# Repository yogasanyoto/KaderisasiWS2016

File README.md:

# KaderisasiWS2016
###Repository untuk keperluan calon kru WS HME ITB 2016
1. **Informasi Umum**
  * Presentasi dan spesifikasi tugas tiap day dapat dilihat pada folder day yang bersesuaian
  * Pembagian kelompok beserta mentor-mentornya dapat dilihat [disini](https://github.com/WorkshopHMEITB/KaderisasiWS2016/blob/master/KelompokCakruWS2016.csv)
  * Kontak mentor dapat dilihat [disini](https://github.com/WorkshopHMEITB/KaderisasiWS2016/blob/master/KontakMentorCakruWS2016.csv)
2. **Aturan umum pengumpulan tugas**
  * Tugas yang sudah selesai harus dipresentasikan kepada mentor masing-masing kelompok pada waktu yang ditentukan bersama mentor sebelum batas waktu yang diberikan pada spesifikasi tugas
  * Tugas harus disertai dengan dokumentasi tugas menggunakan template dokumentasi yang ada pada repository KaderisasiWS2016
  * File-file terkait (yang akan diberitahu pada spesifikasi tiap tugas) beserta dokumentasinya harus dikumpulkan melalui repository KaderisasiWS2016 sebelum batas waktu yang diberikan pada spesifikasi tugas (cara pengumpulan tugas ke repository ada pada poin 3 file ini)
  * Telat mempresentasikan kepada mentor akan mengakibatkan pengurangan nilai total sebesar 5% (telat 1 hari), 15% (telat 2 hari), 30% (telat 3 hari), dan 50% (dengan kata lain tidak dianggap mengumpulkan jika telat lebih dari 4 hari)
3. **Cara pengumpulan tugas**<br  />
 1. Jika anda belum terdaftar di github, klik tombol ***Sign up*** di pojok kanan atas [page ini](https://github.com/WorkshopHMEITB/KaderisasiWS2016) dan ikuti terus prosedurnya hingga anda terdaftar
 2. Jika anda sudah terdaftar, *sign in* dengan menekan tombol ***Sign in*** di pojok kanan atas [page ini](https://github.com/WorkshopHMEITB/KaderisasiWS2016)
 3. Klik tombol ***Fork*** di pojok kanan atas [page ini](https://github.com/WorkshopHMEITB/KaderisasiWS2016)
 4. *Pop up window* akan muncul setelah anda menekan tombol *Fork*, tekan ***profil anda***.
 5. Sekarang, *repository* baru (yang merupakan *forked* repository [WorkshopHMEITB/KaderisasiWS2016](https://github.com/WorkshopHMEITB/KaderisasiWS2016)) akan muncul di profil anda. Alamat repository tersebut akan berbentuk seperti ini: https://github.com/USER_NAME/KaderisasiWS2016, sebagai contoh, https://github.com/fuad1502/KaderisasiWS2016. (Jika anda baru saja mem-*fork* repository WorkshopHMEITB/KaderisasiWS2016, anda akan langsung ter-*redirect* ke alamat repository baru anda tersebut)
 6. Setelah *forked repository* berhasil anda buat, anda dapat ***mengupload file-file*** yang harus anda upload ke repository tersebut. Cara mengupload file yang baik dan benar, ada pada bagian 4, "Cara mengupload file-file ke forked repository"
 7. Setelah semua file yang diperlukan sudah anda upload, tekan ***New Pull Request***
 8. Kemudian tekan tombol ***Create pull request***. Tuliskan "Tugas Day X" pada bagian title dan tekan kembali tombol ***Create pull request***
 9. Selesai. Jika anda sudah mengupload semua file dengan benar, pihak kami akan menerima *pull request* anda dan menggabungkannya ke dalam repository [WorkshopHMEITB/KaderisasiWS2016](https://github.com/WorkshopHMEITB/KaderisasiWS2016)
4. **Cara mengupload file-file ke forked repository**
 1. Buka *forked repository* anda di https://github.com/USER_NAME/KaderisasiWS2016
 2. Buka folder day yang bersesuaian
 3. Buat folder pengumpulan tugas kelompok anda di dalam folder day tersebut dengan cara sebagai berikut
     * Tekan tombol ***Create new file***
     * Pada bagian "Name your file...", tulis "KelompokX" (ganti X dengan nomor kelompok anda), lalu tekan "/". Kemudian, tulis lagi ".gitkeep"
     * *Scroll* kebawah dan klik ***Commit new file***
 4. Pada folder pengumpulan tugas kelompok anda tersebut, klik tombol ***Upload files***
 5. Klik ***choose your files*** dan pilih file mana saja yang ingin anda upload
 6. Setelah semua file berhasil diupload, tekan tombol ***Commit changes***

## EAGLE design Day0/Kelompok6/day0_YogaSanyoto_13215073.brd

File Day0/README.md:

#Tugas Day 0
###*Template file dokumentasi belum ada, kerjakan saja file skematik dan PCB nya dahulu*
1. **Detail Tugas**
  1. Membuat file skematik dari rangkaian di bawah ini menggunakan software Eagle<br  />
  
  2. Membuat file PCB dari skematik yang telah dibuat menggunakan software Eagle
  3. Mencetak 1 buah PCB dari file PCB yang telah dibuat
  4. Membeli komponen-komponen yang dibutuhkan dan memasangnya/menyoldernya pada PCB yang telah dicetak
  5. Membuat dan mengupload file dokumentasi ke folder yang sesuai di repository [KaderisasiWS2016](https://github.com/WorkshopHMEITB/KaderisasiWS2016) (caranya dapat dilihat pada file [README.md](https://github.com/WorkshopHMEITB/KaderisasiWS2016/blob/master/README.md) pada root directory repository)
  6. Mengupload file-file terkait ke folder yang sesuai di repository [KaderisasiWS2016](https://github.com/WorkshopHMEITB/KaderisasiWS2016). File-file yang dimaksud ialah sebagai berikut.
    * File Skematik
    * File PCB
2. **Parameter Penilaian**<br  />
Coming soon...
3. **Deadline**<br  />
Sabtu 17/9/2016 (Namun mengumpulkan minggu tidak dihitung telat satu hari untuk tugas ini, dikarenakan PCB tidak mungkin selesai hari minggu)
4. **Informasi Tambahan**
  * Software Eagle dapat didownload secara gratis sebagai *freeware* dari https://cadsoft.io/
  * Rangkaian yang diberikan diatas sulit untuk dimengerti dikarenakan pengintegrasian 4 komponen transistor dalam rangkaian kedalam satu IC CA3046. Berikut adalah gambar skematik rangkaian diatas apabila keempat transistor digambarkan satu per satu. <br  />
  
  * Tips untuk Mempermudah Pengerjaan
    * Manfaatkan fitur DRC pada pembuatan file PCB untuk memastikan desain yang anda buat dapat dicetak oleh tempat pencetakan anda
    * Gunakan ground plane untuk mempermudah routing (Tidak harus)
    * Gunakan IC header untuk memastikan IC tidak akan rusak saat proses penyolderan, serta agar IC dapat dilepas untuk dipakai dalam hal lain (Tidak harus)
    * Untuk mengurangi biaya mencetak PCB, ketika ingin mencetak, cetak PCB beberapa kelompok secara bersama-sama
    * Cetak maksimal 3 hari sebelum deadline jika pakai masking (Kamis, 15/9/2016), 2 hari jika tidak. Untuk jaga-jaga.
  * Informasi Pencetakan PCB
    * *Spectra* 
      * Lokasi : https://goo.gl/maps/9tBonaAyMZR2
      * Email : kng@bdg.centrin.net.id
      * Telepon : 022 - 7322667
      * Teknologi : Ukuran jalur minimum 0.2 mm (kalau mau aman 0.25 mm)
      * Dapat mencetak langsung ke tempatnya dengan membawa file PCB, atau dapat melalui email dan transfer ATM
    * *MultiKarya* 
      * Lokasi : https://goo.gl/maps/EgyCBrZe8uH2
      * Website : www.multikarya.com
      * Email : pcb_multikarya@yahoo.com
      * Telepon : 022 - 720 2852
      * Teknologi : lihat lengkapnya di http://www.multikarya.com/pcb_technical_indonesia.html
    * *Selc* 
      * Lokasi : https://goo.gl/maps/5XCbfng3uKE2
      * Website : www.selc-komponen.co.id
      * Email : selc@bdg.centrin.net.id
      * Telepon : 022 - 721 0909
      * Teknologi : lihat lengkapnya di http://www.selc-komponen.co.id/index.php?route=information/information&information_id=7)
  * Informasi Pembelian Komponen
    * *Anam* (https://goo.gl/maps/y4qWtzdkQtB2 sebelah Balubur Town Square)
    * *Jaya Plaza* (https://goo.gl/maps/nTADkQ1KY322)<br  />
    Jika kesulitan dalam menemukan CA3046, dapat ditemukan di toko i.want.electronics di Jaya Plaza dengan harga Rp. 27500
    * *Duta Irama* (https://goo.gl/maps/VzKpAT1tsW42 depan Jaya Plaza)
  * Jika ada pertanyaan silakan hubungi [mentor masing-masing](https://github.com/WorkshopHMEITB/KaderisasiWS2016/blob/master/KontakMentorCakruWS2016.csv)

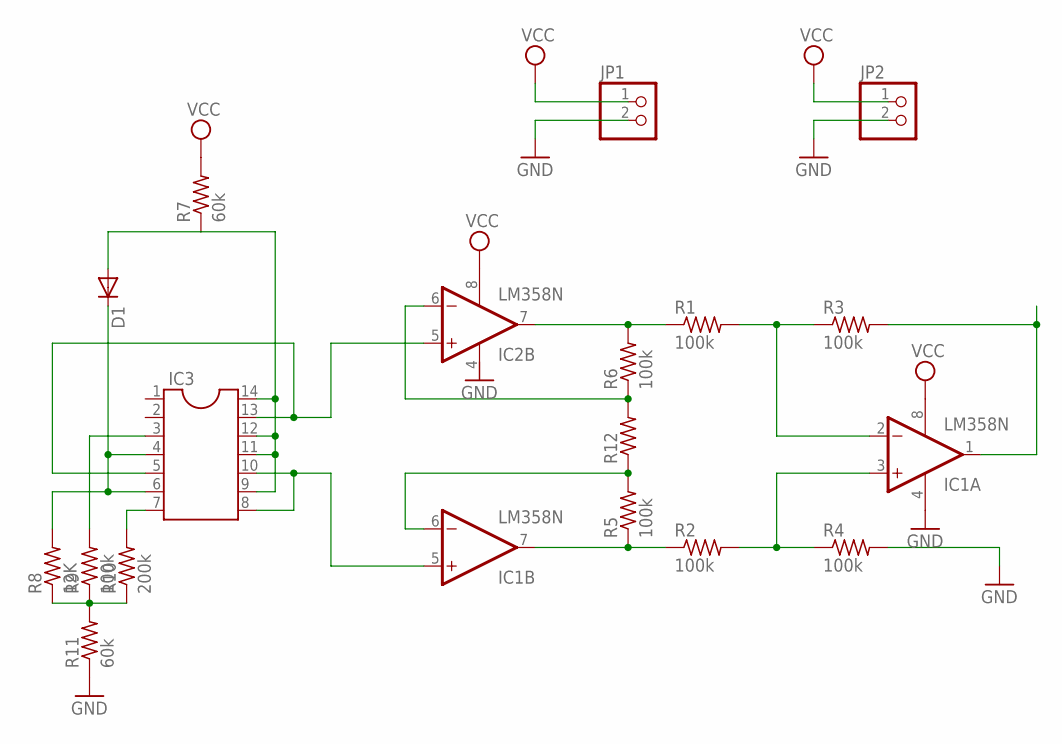
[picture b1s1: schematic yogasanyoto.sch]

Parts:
D1: DIODE-D-7.5; D-7.5
IC1, IC2: LM358N; DIL08
IC3: DIL14
JP1, JP2: PINHD-1X2; 1X02
R1, R2, R3, R4, R5, R6, R9: 100k; 0204/7
R7, R11: 60k; 0204/7
R8: 12K; 0204/7
R10: 200k; 0204/7
R12: R-US_0204/7; 0204/7

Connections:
GND: IC1.4 (V-), JP1.2, JP2.2, R4.2, R11.1
unnamed: R8.1, R9.1, R10.1, R11.2
unnamed: IC3.7, R10.2
unnamed: IC3.3, R9.2
unnamed: D1.C, IC3.4, IC3.6, R8.2
unnamed: D1.A, IC3.9, IC3.11, IC3.12, IC3.14, R7.1
unnamed: IC1.6 (-IN), R5.2, R12.1
unnamed: IC2.6 (-IN), R6.1, R12.2
unnamed: IC2.7 (OUT), R1.1, R6.2
unnamed: IC1.7 (OUT), R2.1, R5.1
unnamed: IC1.2 (-IN), R1.2, R3.1
unnamed: IC1.3 (+IN), R2.2, R4.1
unnamed: IC1.5 (+IN), IC3.8, IC3.10
unnamed: IC2.5 (+IN), IC3.5, IC3.13
V-: IC2.4 (V-)
VCC: IC1.8 (V+), IC2.8 (V+), JP1.1, JP2.1, R7.2
VOUT: IC1.1 (OUT), R3.2

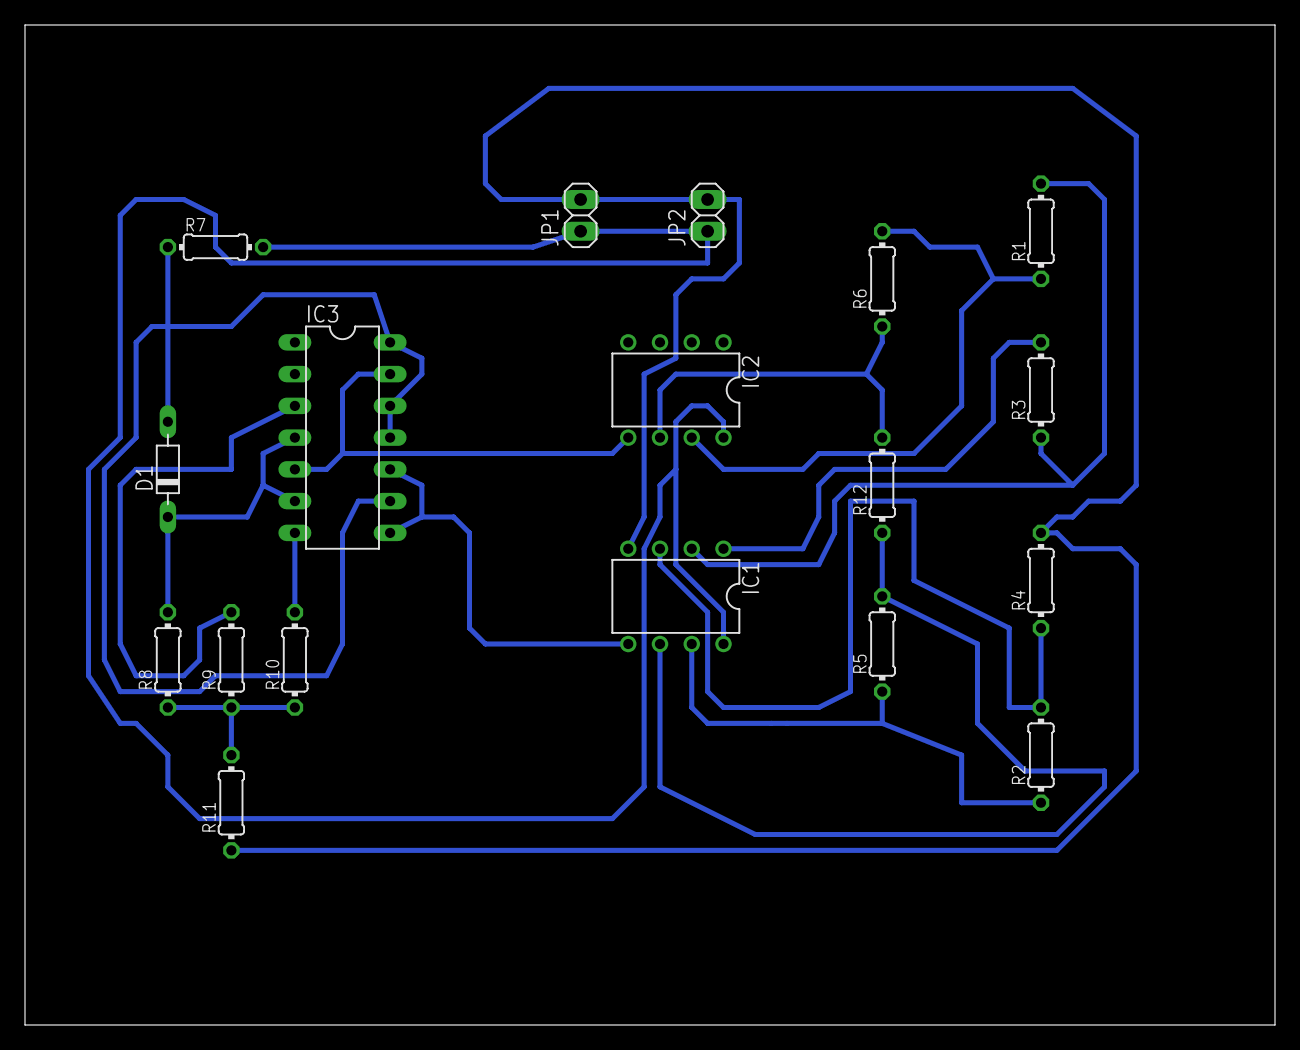
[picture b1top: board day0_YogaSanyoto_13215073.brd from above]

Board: 2 copper layers, 100.0 x 80.0 mm, 18 parts (0 on the bottom side), 16 nets.

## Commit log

2016-09-11 Create KontakMentorWS2016
2016-09-11 Rename KontakMentorWS2016 to KontakMentorWS2016.csv
2016-09-11 Rename KontakMentorWS2016.csv to KontakMentorCakruWS2016.csv
2016-09-20 Create Codes
2016-09-22 Create Yoga Sanyoto
